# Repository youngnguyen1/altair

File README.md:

# altair
My rendition of the Altair keyboard by ai03 Design Studio

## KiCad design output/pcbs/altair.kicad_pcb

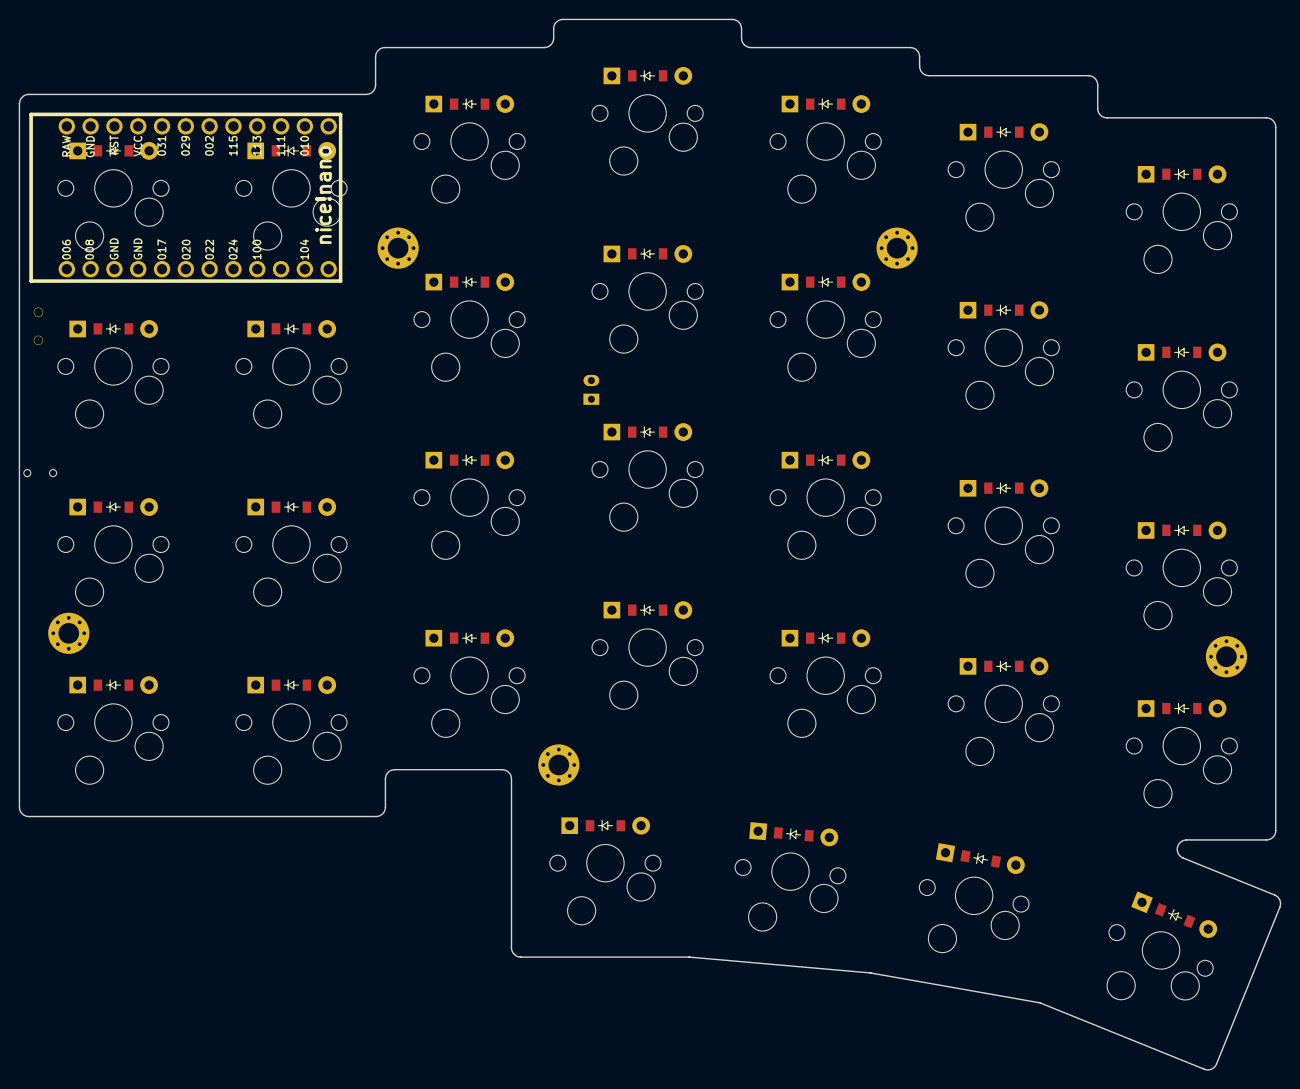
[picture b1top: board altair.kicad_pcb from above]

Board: 2 copper layers, 134.6 x 112.1 mm, 73 parts (0 on the bottom side), 43 nets, no tracks yet.

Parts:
B1: Panasonic_EVQPUL_EVQPUC
D1, D2, D3, D4, D5, D6, D7, D8, D9, D10, D11, D12, D13, D14, D15, D16, D17, D18, D19, D20, D21, D22, D23, D24, D25, D26, D27, D28, D29, D30, D31, D32: ComboDiode
JST1: JST_PH_S2B-PH-K_02x2.00mm_Angled
MCU1: nice_nano
S1, S2, S3, S4, S5, S6, S7, S8, S9, S10, S11, S12, S13, S14, S15, S16, S17, S18, S19, S20, S21, S22, S23, S24, S25, S26, S27, S28, S29, S30, S31, S32: MX
T1: SPDT_C128955
_1, _2, _3, _4, _5: MountingHole_2.2mm_M2_Pad_Via

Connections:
GND: B1.1, JST1.2, MCU1.3, MCU1.4, MCU1.23
P009: MCU1.13, S17.1, S18.1, S19.1, S20.1, S30.1
P010: MCU1.14, S13.1, S14.1, S15.1, S16.1, S29.1
P020: MCU1.6, S1.1, S2.1, S3.1, S4.1
P029: MCU1.19, S21.1, S22.1, S23.1, S24.1, S31.1
P031: MCU1.20, S25.1, S26.1, S27.1, S28.1, S32.1
P106: MCU1.12, S5.1, S6.1, S7.1, S8.1
P111: MCU1.15, S9.1, S10.1, S11.1, S12.1
RAW: MCU1.24, T1.2
RST: B1.2, MCU1.22
far_thumb: D31.2, S31.2
home_thumb: D30.2, S30.2
index_bottom: D17.2, S17.2
index_home: D18.2, S18.2
index_num: D20.2, S20.2
index_top: D19.2, S19.2
inner_bottom: D21.2, S21.2
inner_home: D22.2, S22.2
inner_num: D24.2, S24.2
inner_top: D23.2, S23.2
left_bottom: D1.2, S1.2
left_home: D2.2, S2.2
left_num: D4.2, S4.2
left_thumb: D29.2, S29.2
left_top: D3.2, S3.2
middle_bottom: D13.2, S13.2
middle_home: D14.2, S14.2
middle_num: D16.2, S16.2
middle_top: D15.2, S15.2
out_thumb: D32.2, S32.2
pinky_bottom: D5.2, S5.2
pinky_home: D6.2, S6.2
pinky_num: D8.2, S8.2
pinky_top: D7.2, S7.2
pos: JST1.1, T1.1
right_bottom: D25.2, S25.2
right_home: D26.2, S26.2
right_num: D28.2, S28.2
right_top: D27.2, S27.2
ring_bottom: D9.2, S9.2
ring_home: D10.2, S10.2
ring_num: D12.2, S12.2
ring_top: D11.2, S11.2

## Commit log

2024-11-10 add altair config yaml file
2024-11-10 Generate KiCAD files
2024-11-12 update yaml file
2024-11-12 Switch over to local ergogen from web UI for custom footprints
2024-11-12 Create column and row nets. Change position of MCU
2024-11-12 create starting point for case
2024-11-13 Change column and row nets
